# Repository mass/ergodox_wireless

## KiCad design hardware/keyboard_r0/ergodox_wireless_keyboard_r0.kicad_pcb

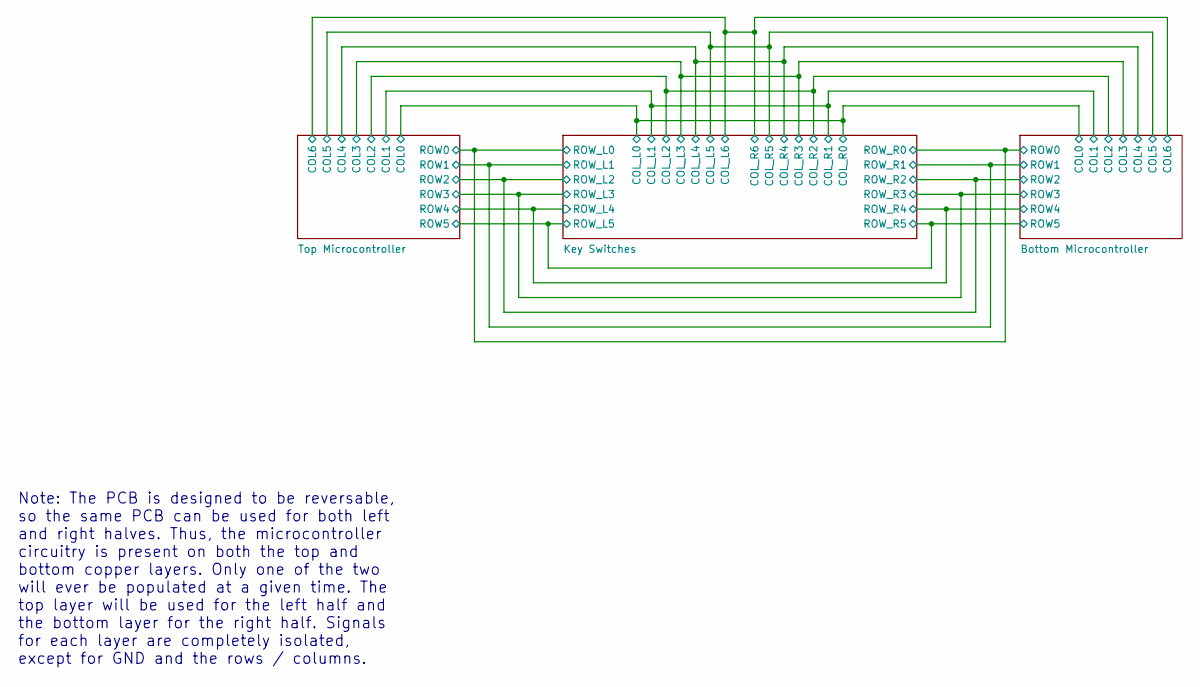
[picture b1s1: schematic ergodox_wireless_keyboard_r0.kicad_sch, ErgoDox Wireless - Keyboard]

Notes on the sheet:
Note: The PCB is designed to be reversable, so the same PCB can be used for both left and right halves. Thus, the microcontroller circuitry is present on both the top and bottom copper layers. Only one of the two will ever be populated at a given time. The top layer will be used for the left half a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

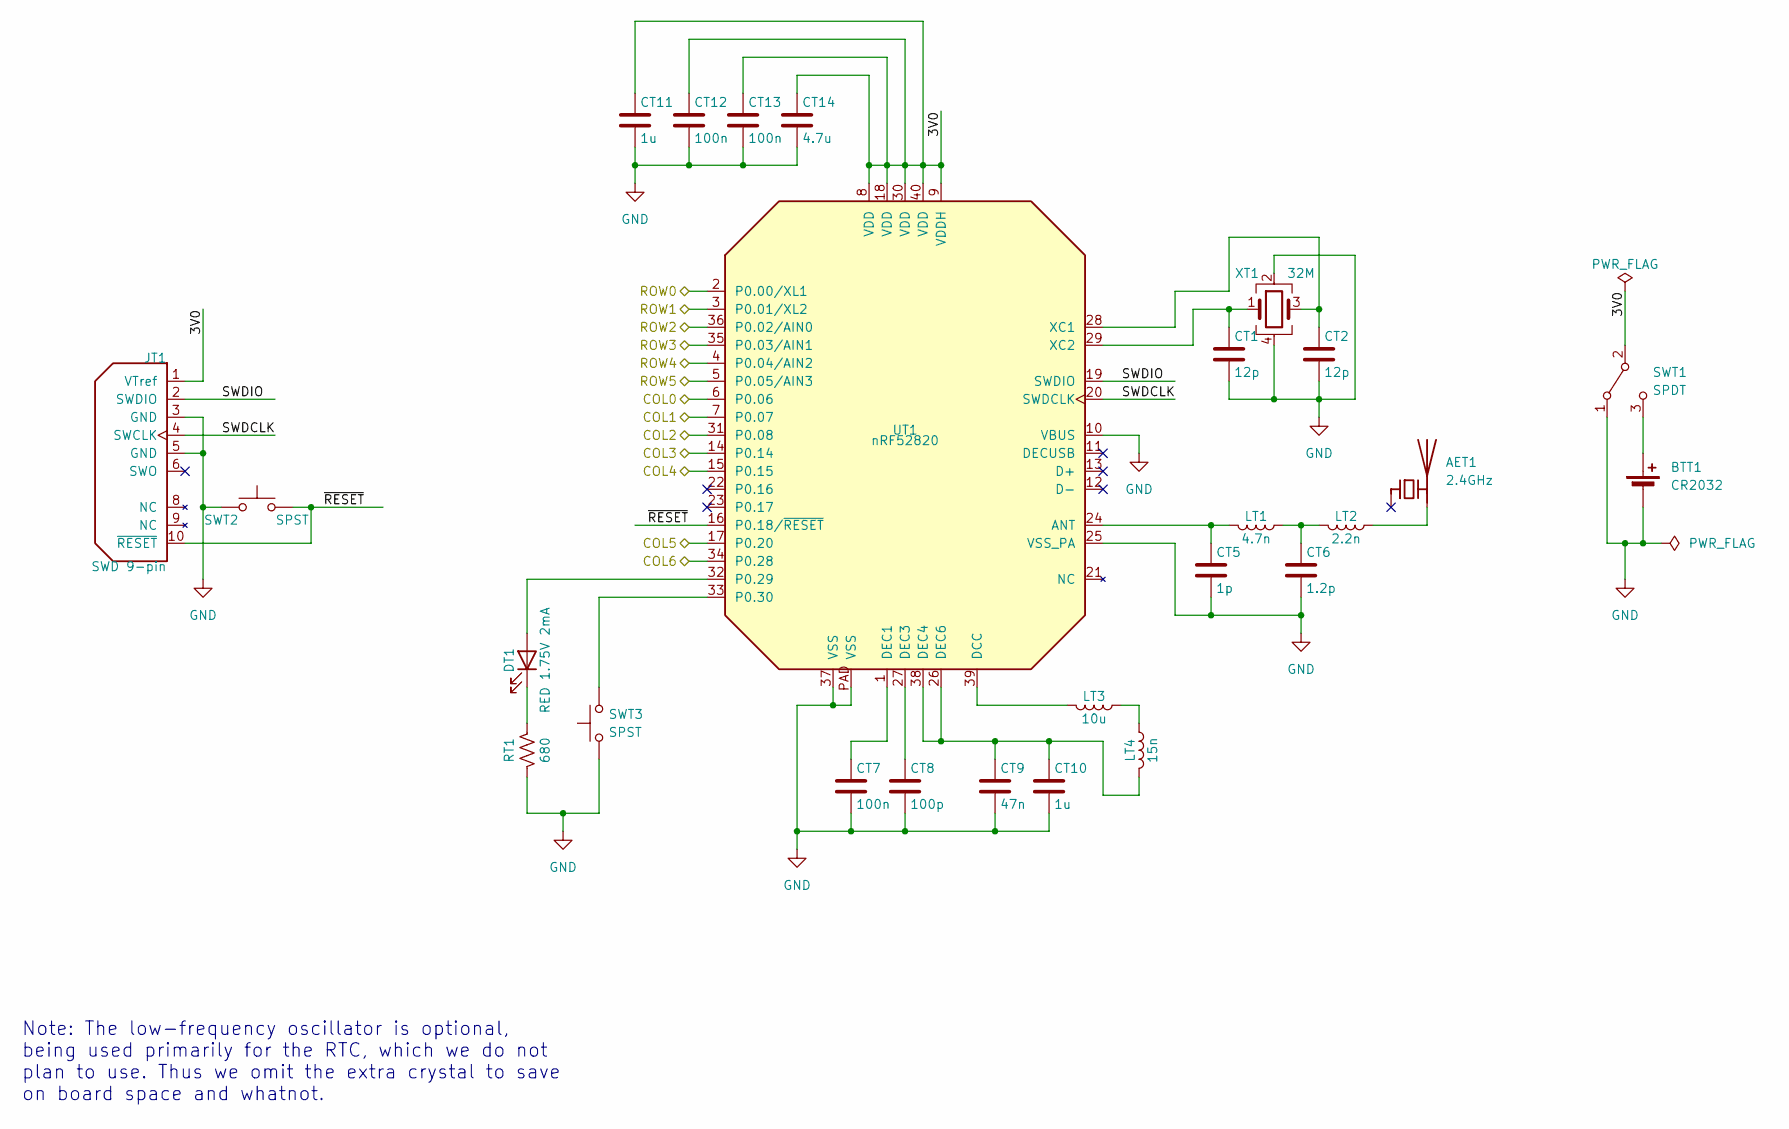
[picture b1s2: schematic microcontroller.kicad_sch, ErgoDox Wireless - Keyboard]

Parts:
AET1: 2.4GHz; 2450AT18A100E
BTT1: CR2032; BU2032SM-BT-GTR
CT1, CT2: 12p; 0603
CT5: 1p; 0402
CT6: 1.2p; 0402
CT7, CT12, CT13: 100n; 0603
CT8: 100p; 0603
CT9: 47n; 0603
CT10, CT11: 1u; 0603
CT14: 4.7u; 0603
DT1: RED 1.75V 2mA; LED_0603_1608Metric_Pad1.05x0.95mm_HandSolder
JT1: SWD 9-pin; SAMTEC_FTSH-105-01-L-DV-007
LT1: 4.7n; 0402
LT2: 2.2n; 0402
LT3: 10u; 0603
LT4: 15n; 0603
RT1: 680; 0603
SWT1: SPDT; JS102011SCQN
SWT2, SWT3: SPST; 430152043836
UT1: nRF52820; QFN-40
XT1: 32M; TSX-3225

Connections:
/Bottom Microcontroller/COL0: UT1.6 (P0.06); also elsewhere on the board
/Bottom Microcontroller/COL1: UT1.7 (P0.07); also elsewhere on the board
/Bottom Microcontroller/COL2: UT1.31 (P0.08); also elsewhere on the board
/Bottom Microcontroller/COL3: UT1.14 (P0.14); also elsewhere on the board
/Bottom Microcontroller/COL4: UT1.15 (P0.15); also elsewhere on the board
/Bottom Microcontroller/COL5: UT1.17 (P0.20); also elsewhere on the board
/Bottom Microcontroller/COL6: UT1.34 (P0.28); also elsewhere on the board
/Bottom Microcontroller/ROW0: UT1.2 (P0.00/XL1); also elsewhere on the board
/Bottom Microcontroller/ROW1: UT1.3 (P0.01/XL2); also elsewhere on the board
/Bottom Microcontroller/ROW2: UT1.36 (P0.02/AIN0); also elsewhere on the board
/Bottom Microcontroller/ROW3: UT1.35 (P0.03/AIN1); also elsewhere on the board
/Bottom Microcontroller/ROW4: UT1.4 (P0.04/AIN2); also elsewhere on the board
/Bottom Microcontroller/ROW5: UT1.5 (P0.05/AIN3); also elsewhere on the board
/Top Microcontroller/3V0: CT11.1, CT12.1, CT13.1, CT14.1, JT1.1 (VTref), SWT1.2 (B), UT1.8 (VDD), UT1.9 (VDDH), UT1.18 (VDD), UT1.30 (VDD), UT1.40 (VDD)
/Top Microcontroller/SWDCLK: JT1.4 (SWCLK), UT1.20 (SWDCLK)
/Top Microcontroller/SWDIO: JT1.2 (SWDIO), UT1.19 (SWDIO)
/Top Microcontroller/~RESET: JT1.10 (~RESET), SWT2.1, UT1.16 (P0.18/~RESET)
GND: BTT1.2 (-), CT1.2, CT2.2, CT5.2, CT6.2, CT7.2, CT8.2, CT9.2, CT10.2, CT11.2, CT12.2, CT13.2, CT14.2, JT1.3 (GND), JT1.5 (GND), RT1.2, SWT1.1 (A), SWT2.2, SWT3.1, UT1.10 (VBUS), UT1.25 (VSS_PA), UT1.37 (VSS), UT1.PAD (VSS), XT1.2, XT1.4; also elsewhere on the board
unnamed: AET1.2 (PCB_Trace), LT2.2
unnamed: BTT1.1 (+), SWT1.3 (C)
unnamed: CT6.1, LT1.2, LT2.1
unnamed: DT1.2 (A), UT1.32 (P0.29)
unnamed: DT1.1 (K), RT1.1
unnamed: LT3.2, LT4.1
unnamed: CT5.1, LT1.1, UT1.24 (ANT)
unnamed: LT3.1, UT1.39 (DCC)
unnamed: CT7.1, UT1.1 (DEC1)
unnamed: CT8.1, UT1.27 (DEC3)
unnamed: CT9.1, CT10.1, LT4.2, UT1.26 (DEC6), UT1.38 (DEC4)
unnamed: SWT3.2, UT1.33 (P0.30)
unnamed: CT2.1, UT1.28 (XC1), XT1.3
unnamed: CT1.1, UT1.29 (XC2), XT1.1

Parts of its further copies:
AEB1: 2.4GHz; 2450AT18A100E
BTB1: CR2032; BU2032SM-BT-GTR
CB1, CB2: 12p; 0603
CB5: 1p; 0402
CB6: 1.2p; 0402
CB7, CB12, CB13: 100n; 0603
CB8: 100p; 0603
CB9: 47n; 0603
CB10, CB11: 1u; 0603
CB14: 4.7u; 0603
DB1: RED 1.75V 2mA; LED_0603_1608Metric_Pad1.05x0.95mm_HandSolder
JB1: SWD 9-pin; SAMTEC_FTSH-105-01-L-DV-007
LB1: 4.7n; 0402
LB2: 2.2n; 0402
LB3: 10u; 0603
LB4: 15n; 0603
RB1: 680; 0603
SWB1: SPDT; JS102011SCQN
SWB2, SWB3: SPST; 430152043836
UB1: nRF52820; QFN-40
XB1: 32M; TSX-3225

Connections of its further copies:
/Bottom Microcontroller/3V0: CB11.1, CB12.1, CB13.1, CB14.1, JB1.1 (VTref), SWB1.2 (B), UB1.8 (VDD), UB1.9 (VDDH), UB1.18 (VDD), UB1.30 (VDD), UB1.40 (VDD)
/Bottom Microcontroller/COL0: UB1.6 (P0.06); also elsewhere on the board
/Bottom Microcontroller/COL1: UB1.7 (P0.07); also elsewhere on the board
/Bottom Microcontroller/COL2: UB1.31 (P0.08); also elsewhere on the board
/Bottom Microcontroller/COL3: UB1.14 (P0.14); also elsewhere on the board
/Bottom Microcontroller/COL4: UB1.15 (P0.15); also elsewhere on the board
/Bottom Microcontroller/COL5: UB1.17 (P0.20); also elsewhere on the board
/Bottom Microcontroller/COL6: UB1.34 (P0.28); also elsewhere on the board
/Bottom Microcontroller/ROW0: UB1.2 (P0.00/XL1); also elsewhere on the board
/Bottom Microcontroller/ROW1: UB1.3 (P0.01/XL2); also elsewhere on the board
/Bottom Microcontroller/ROW2: UB1.36 (P0.02/AIN0); also elsewhere on the board
/Bottom Microcontroller/ROW3: UB1.35 (P0.03/AIN1); also elsewhere on the board
/Bottom Microcontroller/ROW4: UB1.4 (P0.04/AIN2); also elsewhere on the board
/Bottom Microcontroller/ROW5: UB1.5 (P0.05/AIN3); also elsewhere on the board
/Bottom Microcontroller/SWDCLK: JB1.4 (SWCLK), UB1.20 (SWDCLK)
/Bottom Microcontroller/SWDIO: JB1.2 (SWDIO), UB1.19 (SWDIO)
/Bottom Microcontroller/~RESET: JB1.10 (~RESET), SWB2.1, UB1.16 (P0.18/~RESET)
GND: BTB1.2 (-), CB1.2, CB2.2, CB5.2, CB6.2, CB7.2, CB8.2, CB9.2, CB10.2, CB11.2, CB12.2, CB13.2, CB14.2, JB1.3 (GND), JB1.5 (GND), RB1.2, SWB1.1 (A), SWB2.2, SWB3.1, UB1.10 (VBUS), UB1.25 (VSS_PA), UB1.37 (VSS), UB1.PAD (VSS), XB1.2, XB1.4; also elsewhere on the board
unnamed: AEB1.2 (PCB_Trace), LB2.2
unnamed: BTB1.1 (+), SWB1.3 (C)
unnamed: CB6.1, LB1.2, LB2.1
unnamed: DB1.2 (A), UB1.32 (P0.29)
unnamed: DB1.1 (K), RB1.1
unnamed: LB3.2, LB4.1
unnamed: CB5.1, LB1.1, UB1.24 (ANT)
unnamed: LB3.1, UB1.39 (DCC)
unnamed: CB7.1, UB1.1 (DEC1)
unnamed: CB8.1, UB1.27 (DEC3)
unnamed: CB9.1, CB10.1, LB4.2, UB1.26 (DEC6), UB1.38 (DEC4)
unnamed: SWB3.2, UB1.33 (P0.30)
unnamed: CB2.1, UB1.28 (XC1), XB1.3
unnamed: CB1.1, UB1.29 (XC2), XB1.1

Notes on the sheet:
Note: The low-frequency oscillator is optional, being used primarily for the RTC, which we do not plan to use. Thus we omit the extra crystal to save on board space and whatnot.

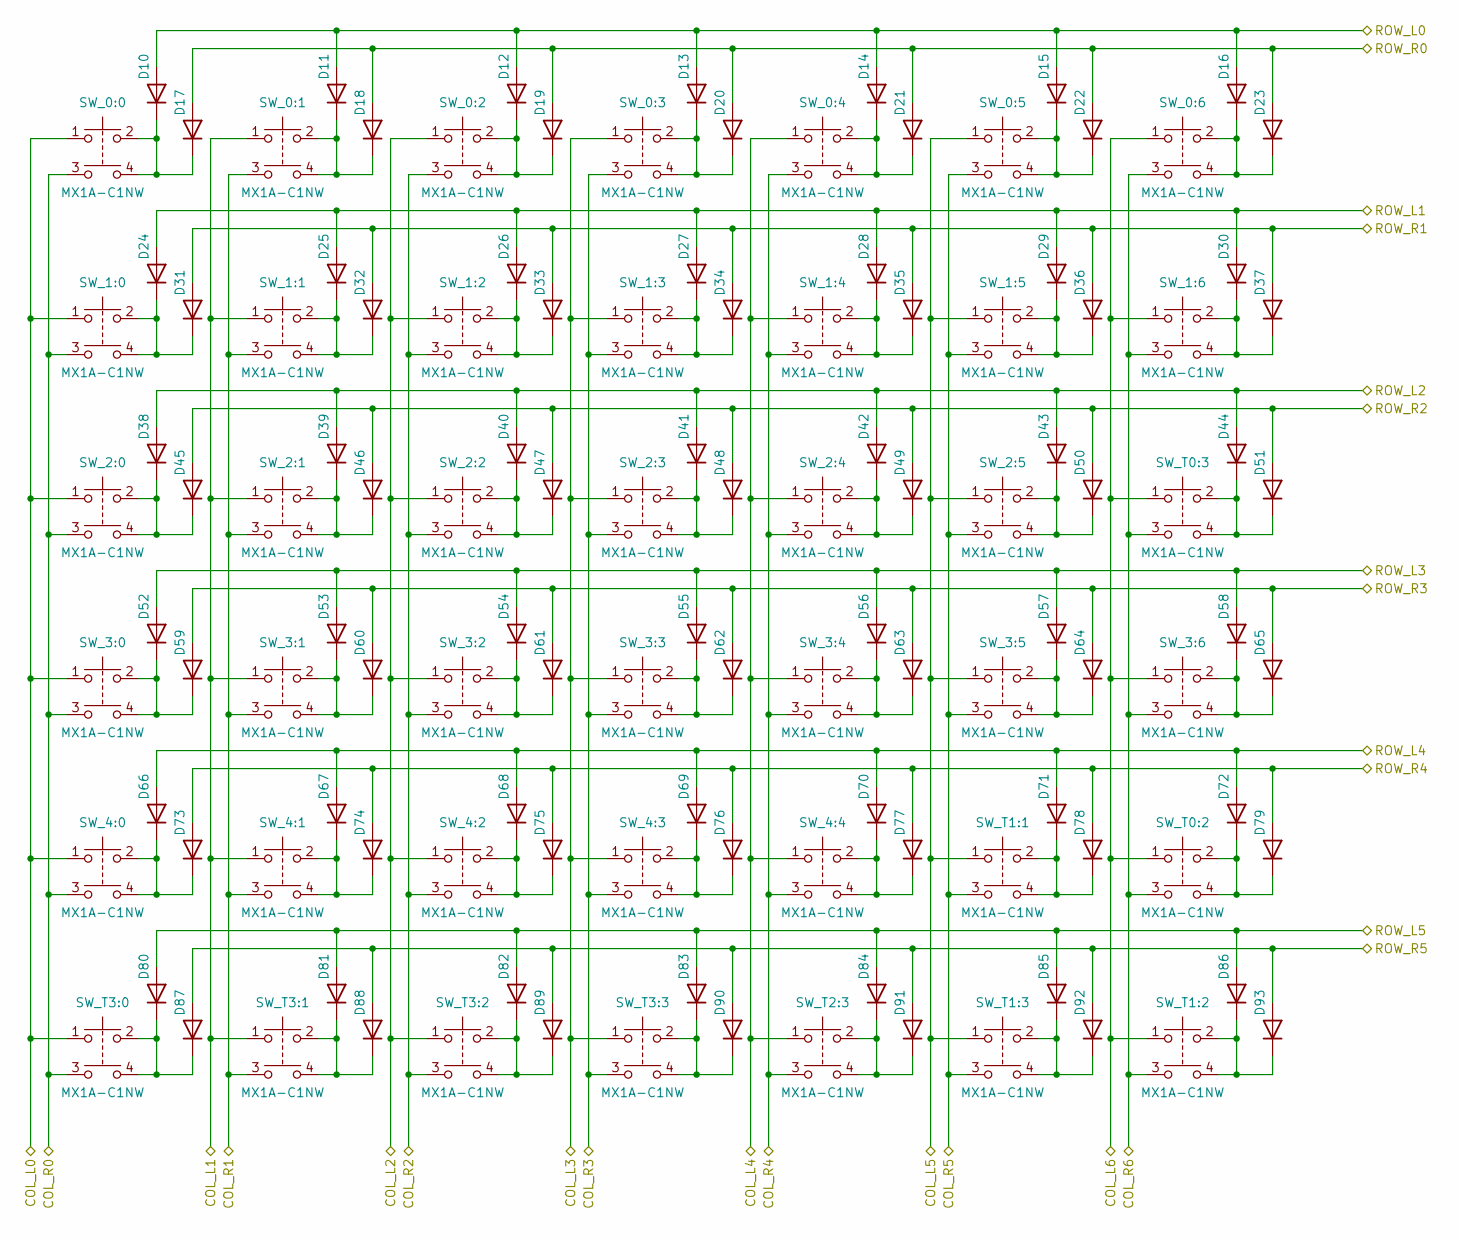
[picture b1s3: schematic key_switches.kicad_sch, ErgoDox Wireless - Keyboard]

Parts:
D10, D11, D12, D13, D14, D15, D16, D17, D18, D19, D20, D21, D22, D23, D24, D25, D26, D27, D28, D29, D30, D31, D32, D33, D34, D35, D36, D37, D38, D39, D40, D41, D42, D43, D44, D45, D46, D47, D48, D49, D50, D51, D52, D53, D54, D55, D56, D57, D58, D59, D60, D61, D62, D63, D64, D65, D66, D67, D68, D69, D70, D71, D72, D73, D74, D75, D76, D77, D78, D79, D80, D81, D82, D83, D84, D85, D86, D87, D88, D89, D90, D91, D92, D93: D; D_SOD-123
SW_0:0, SW_1:0, SW_2:0, SW_3:0, SW_4:0: MX1A-C1NW; MX1A-C1NW-1.5U
SW_0:1, SW_0:2, SW_0:3, SW_0:4, SW_0:5, SW_0:6, SW_1:1, SW_1:2, SW_1:3, SW_1:4, SW_1:5, SW_2:1, SW_2:2, SW_2:3, SW_2:4, SW_2:5, SW_3:1, SW_3:2, SW_3:3, SW_3:4, SW_3:5, SW_4:1, SW_4:2, SW_4:3, SW_4:4: MX1A-C1NW; MX1A-C1NW-1U
SW_1:6, SW_3:6: MX1A-C1NW; MX1A-C1NW-1.5U-V
SW_T0:2, SW_T0:3, SW_T1:3, SW_T2:3, SW_T3:0, SW_T3:1, SW_T3:2, SW_T3:3: MX1A-C1NW; MX1A-C1NW-1U
SW_T1:1, SW_T1:2: MX1A-C1NW; MX1A-C1NW-2U-V

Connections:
/Bottom Microcontroller/COL0: SW_0:0.1, SW_0:0.3, SW_1:0.1, SW_1:0.3, SW_2:0.1, SW_2:0.3, SW_3:0.1, SW_3:0.3, SW_4:0.1, SW_4:0.3, SW_T3:0.1, SW_T3:0.3; also elsewhere on the board
/Bottom Microcontroller/COL1: SW_0:1.1, SW_0:1.3, SW_1:1.1, SW_1:1.3, SW_2:1.1, SW_2:1.3, SW_3:1.1, SW_3:1.3, SW_4:1.1, SW_4:1.3, SW_T3:1.1, SW_T3:1.3; also elsewhere on the board
/Bottom Microcontroller/COL2: SW_0:2.1, SW_0:2.3, SW_1:2.1, SW_1:2.3, SW_2:2.1, SW_2:2.3, SW_3:2.1, SW_3:2.3, SW_4:2.1, SW_4:2.3, SW_T3:2.1, SW_T3:2.3; also elsewhere on the board
/Bottom Microcontroller/COL3: SW_0:3.1, SW_0:3.3, SW_1:3.1, SW_1:3.3, SW_2:3.1, SW_2:3.3, SW_3:3.1, SW_3:3.3, SW_4:3.1, SW_4:3.3, SW_T3:3.1, SW_T3:3.3; also elsewhere on the board
/Bottom Microcontroller/COL4: SW_0:4.1, SW_0:4.3, SW_1:4.1, SW_1:4.3, SW_2:4.1, SW_2:4.3, SW_3:4.1, SW_3:4.3, SW_4:4.1, SW_4:4.3, SW_T2:3.1, SW_T2:3.3; also elsewhere on the board
/Bottom Microcontroller/COL5: SW_0:5.1, SW_0:5.3, SW_1:5.1, SW_1:5.3, SW_2:5.1, SW_2:5.3, SW_3:5.1, SW_3:5.3, SW_T1:1.1, SW_T1:1.3, SW_T1:3.1, SW_T1:3.3; also elsewhere on the board
/Bottom Microcontroller/COL6: SW_0:6.1, SW_0:6.3, SW_1:6.1, SW_1:6.3, SW_3:6.1, SW_3:6.3, SW_T0:2.1, SW_T0:2.3, SW_T0:3.1, SW_T0:3.3, SW_T1:2.1, SW_T1:2.3; also elsewhere on the board
/Bottom Microcontroller/ROW0: D10.2 (A), D11.2 (A), D12.2 (A), D13.2 (A), D14.2 (A), D15.2 (A), D16.2 (A), D17.2 (A), D18.2 (A), D19.2 (A), D20.2 (A), D21.2 (A), D22.2 (A), D23.2 (A); also elsewhere on the board
/Bottom Microcontroller/ROW1: D24.2 (A), D25.2 (A), D26.2 (A), D27.2 (A), D28.2 (A), D29.2 (A), D30.2 (A), D31.2 (A), D32.2 (A), D33.2 (A), D34.2 (A), D35.2 (A), D36.2 (A), D37.2 (A); also elsewhere on the board
/Bottom Microcontroller/ROW2: D38.2 (A), D39.2 (A), D40.2 (A), D41.2 (A), D42.2 (A), D43.2 (A), D44.2 (A), D45.2 (A), D46.2 (A), D47.2 (A), D48.2 (A), D49.2 (A), D50.2 (A), D51.2 (A); also elsewhere on the board
/Bottom Microcontroller/ROW3: D52.2 (A), D53.2 (A), D54.2 (A), D55.2 (A), D56.2 (A), D57.2 (A), D58.2 (A), D59.2 (A), D60.2 (A), D61.2 (A), D62.2 (A), D63.2 (A), D64.2 (A), D65.2 (A); also elsewhere on the board
/Bottom Microcontroller/ROW4: D66.2 (A), D67.2 (A), D68.2 (A), D69.2 (A), D70.2 (A), D71.2 (A), D72.2 (A), D73.2 (A), D74.2 (A), D75.2 (A), D76.2 (A), D77.2 (A), D78.2 (A), D79.2 (A); also elsewhere on the board
/Bottom Microcontroller/ROW5: D80.2 (A), D81.2 (A), D82.2 (A), D83.2 (A), D84.2 (A), D85.2 (A), D86.2 (A), D87.2 (A), D88.2 (A), D89.2 (A), D90.2 (A), D91.2 (A), D92.2 (A), D93.2 (A); also elsewhere on the board
unnamed: D10.1 (K), D17.1 (K), SW_0:0.2, SW_0:0.4
unnamed: D11.1 (K), D18.1 (K), SW_0:1.2, SW_0:1.4
unnamed: D12.1 (K), D19.1 (K), SW_0:2.2, SW_0:2.4
unnamed: D13.1 (K), D20.1 (K), SW_0:3.2, SW_0:3.4
unnamed: D14.1 (K), D21.1 (K), SW_0:4.2, SW_0:4.4
unnamed: D15.1 (K), D22.1 (K), SW_0:5.2, SW_0:5.4
unnamed: D16.1 (K), D23.1 (K), SW_0:6.2, SW_0:6.4
unnamed: D24.1 (K), D31.1 (K), SW_1:0.2, SW_1:0.4
unnamed: D25.1 (K), D32.1 (K), SW_1:1.2, SW_1:1.4
unnamed: D26.1 (K), D33.1 (K), SW_1:2.2, SW_1:2.4
unnamed: D27.1 (K), D34.1 (K), SW_1:3.2, SW_1:3.4
unnamed: D28.1 (K), D35.1 (K), SW_1:4.2, SW_1:4.4
unnamed: D29.1 (K), D36.1 (K), SW_1:5.2, SW_1:5.4
unnamed: D30.1 (K), D37.1 (K), SW_1:6.2, SW_1:6.4
unnamed: D38.1 (K), D45.1 (K), SW_2:0.2, SW_2:0.4
unnamed: D39.1 (K), D46.1 (K), SW_2:1.2, SW_2:1.4
unnamed: D40.1 (K), D47.1 (K), SW_2:2.2, SW_2:2.4
unnamed: D41.1 (K), D48.1 (K), SW_2:3.2, SW_2:3.4
unnamed: D42.1 (K), D49.1 (K), SW_2:4.2, SW_2:4.4
unnamed: D43.1 (K), D50.1 (K), SW_2:5.2, SW_2:5.4
unnamed: D44.1 (K), D51.1 (K), SW_T0:3.2, SW_T0:3.4
unnamed: D52.1 (K), D59.1 (K), SW_3:0.2, SW_3:0.4
unnamed: D53.1 (K), D60.1 (K), SW_3:1.2, SW_3:1.4
unnamed: D54.1 (K), D61.1 (K), SW_3:2.2, SW_3:2.4
unnamed: D55.1 (K), D62.1 (K), SW_3:3.2, SW_3:3.4
unnamed: D56.1 (K), D63.1 (K), SW_3:4.2, SW_3:4.4
unnamed: D57.1 (K), D64.1 (K), SW_3:5.2, SW_3:5.4
unnamed: D58.1 (K), D65.1 (K), SW_3:6.2, SW_3:6.4
unnamed: D66.1 (K), D73.1 (K), SW_4:0.2, SW_4:0.4
unnamed: D67.1 (K), D74.1 (K), SW_4:1.2, SW_4:1.4
unnamed: D68.1 (K), D75.1 (K), SW_4:2.2, SW_4:2.4
unnamed: D69.1 (K), D76.1 (K), SW_4:3.2, SW_4:3.4
unnamed: D70.1 (K), D77.1 (K), SW_4:4.2, SW_4:4.4
unnamed: D71.1 (K), D78.1 (K), SW_T1:1.2, SW_T1:1.4
unnamed: D72.1 (K), D79.1 (K), SW_T0:2.2, SW_T0:2.4
unnamed: D80.1 (K), D87.1 (K), SW_T3:0.2, SW_T3:0.4
unnamed: D81.1 (K), D88.1 (K), SW_T3:1.2, SW_T3:1.4
unnamed: D82.1 (K), D89.1 (K), SW_T3:2.2, SW_T3:2.4
unnamed: D83.1 (K), D90.1 (K), SW_T3:3.2, SW_T3:3.4
unnamed: D84.1 (K), D91.1 (K), SW_T2:3.2, SW_T2:3.4
unnamed: D85.1 (K), D92.1 (K), SW_T1:3.2, SW_T1:3.4
unnamed: D86.1 (K), D93.1 (K), SW_T1:2.2, SW_T1:2.4

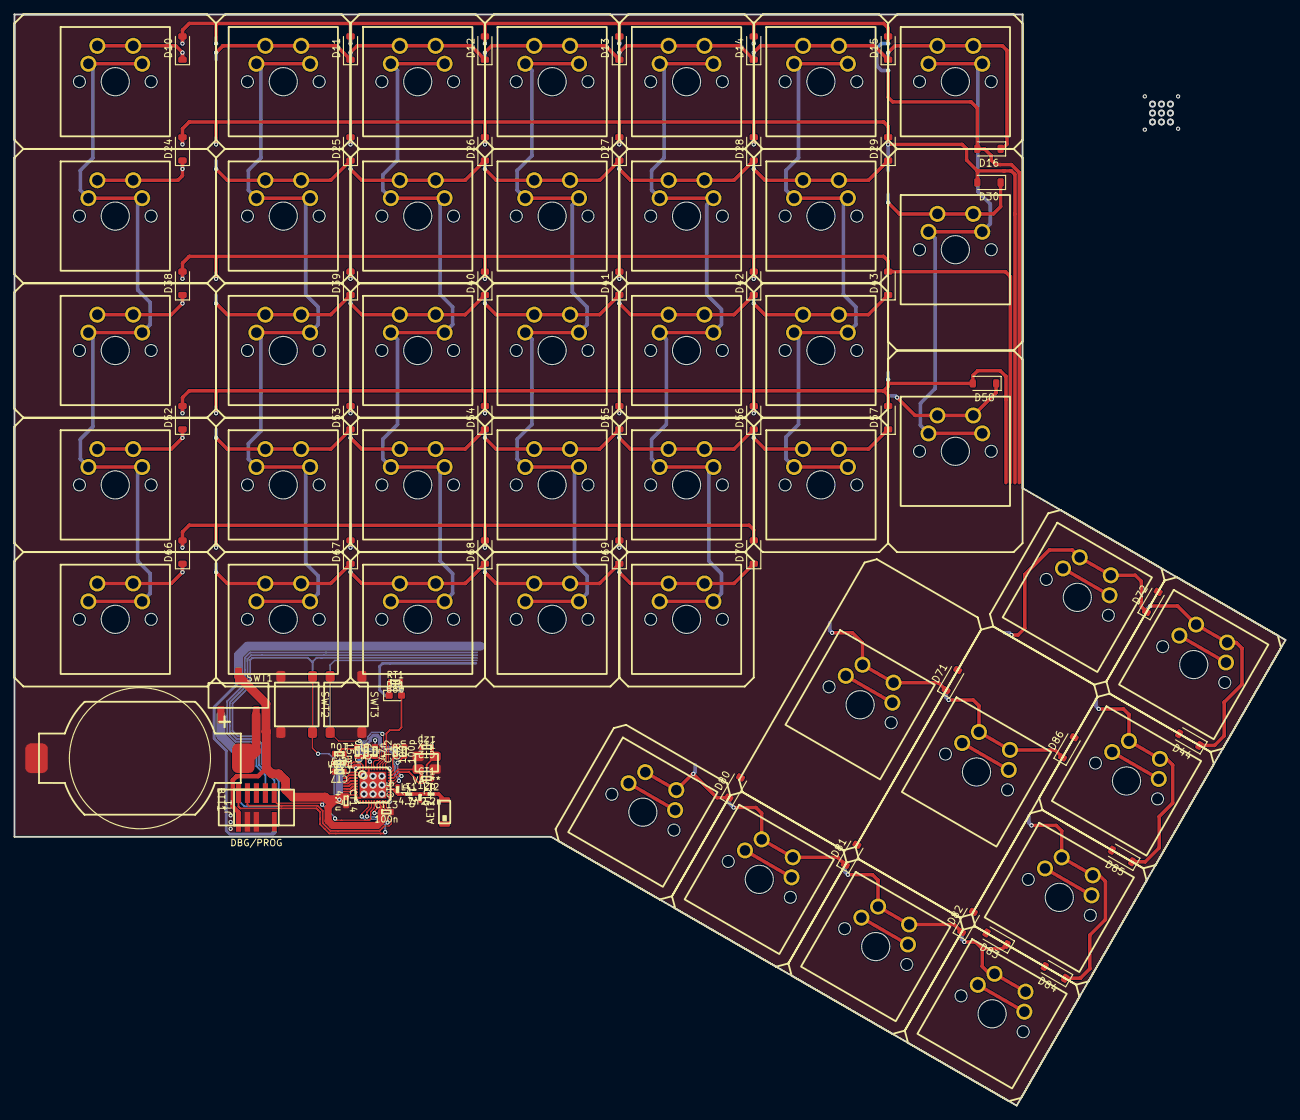
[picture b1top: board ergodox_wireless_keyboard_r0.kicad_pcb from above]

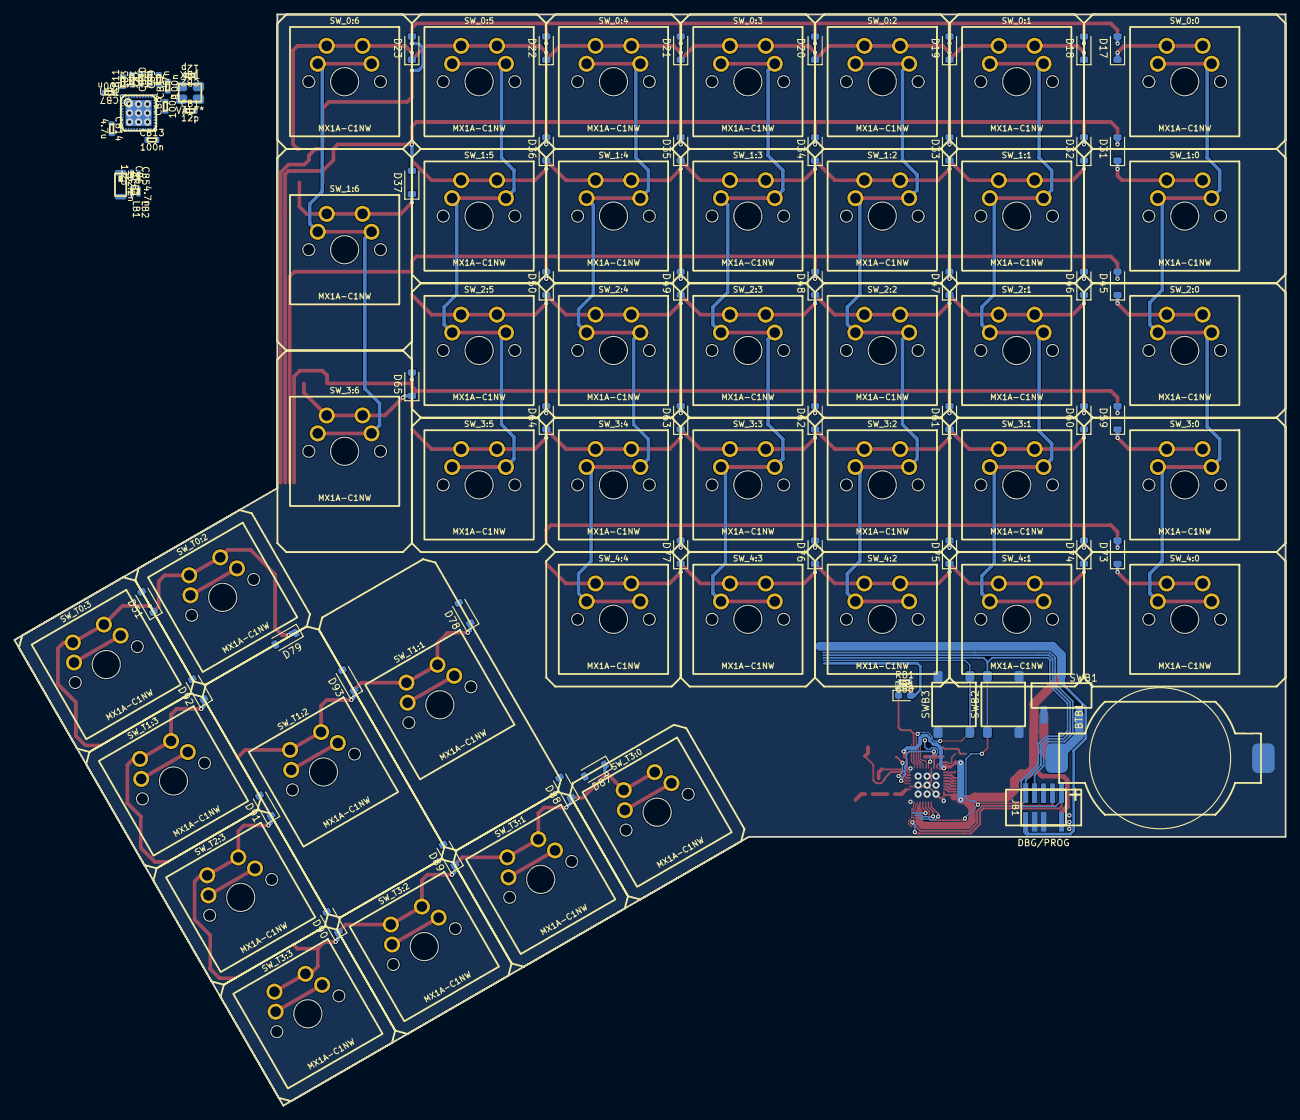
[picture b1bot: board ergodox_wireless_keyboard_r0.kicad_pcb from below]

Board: 2 copper layers, 180.1 x 154.6 mm, 178 parts (68 on the bottom side), 92 nets.

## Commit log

2023-02-06 Initial commit.
    Add kicad files for keyboard_r0, along with general structure
2025-01-07 Use custom copy of SW_Push_Dual symbol.
2025-01-07 Remaining schematic updates from 8.0 migration.
2025-01-07 Update PCB to KiCAD 8.0.
2025-01-08 Remove optional low-frequency oscillator circuit.
2025-01-09 Begin to route traces around the microcontroller.
2025-01-11 Finish routing most of the top micro circuits
